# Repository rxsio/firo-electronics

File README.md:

# Hello
This is a test README to confirm proper branch setup

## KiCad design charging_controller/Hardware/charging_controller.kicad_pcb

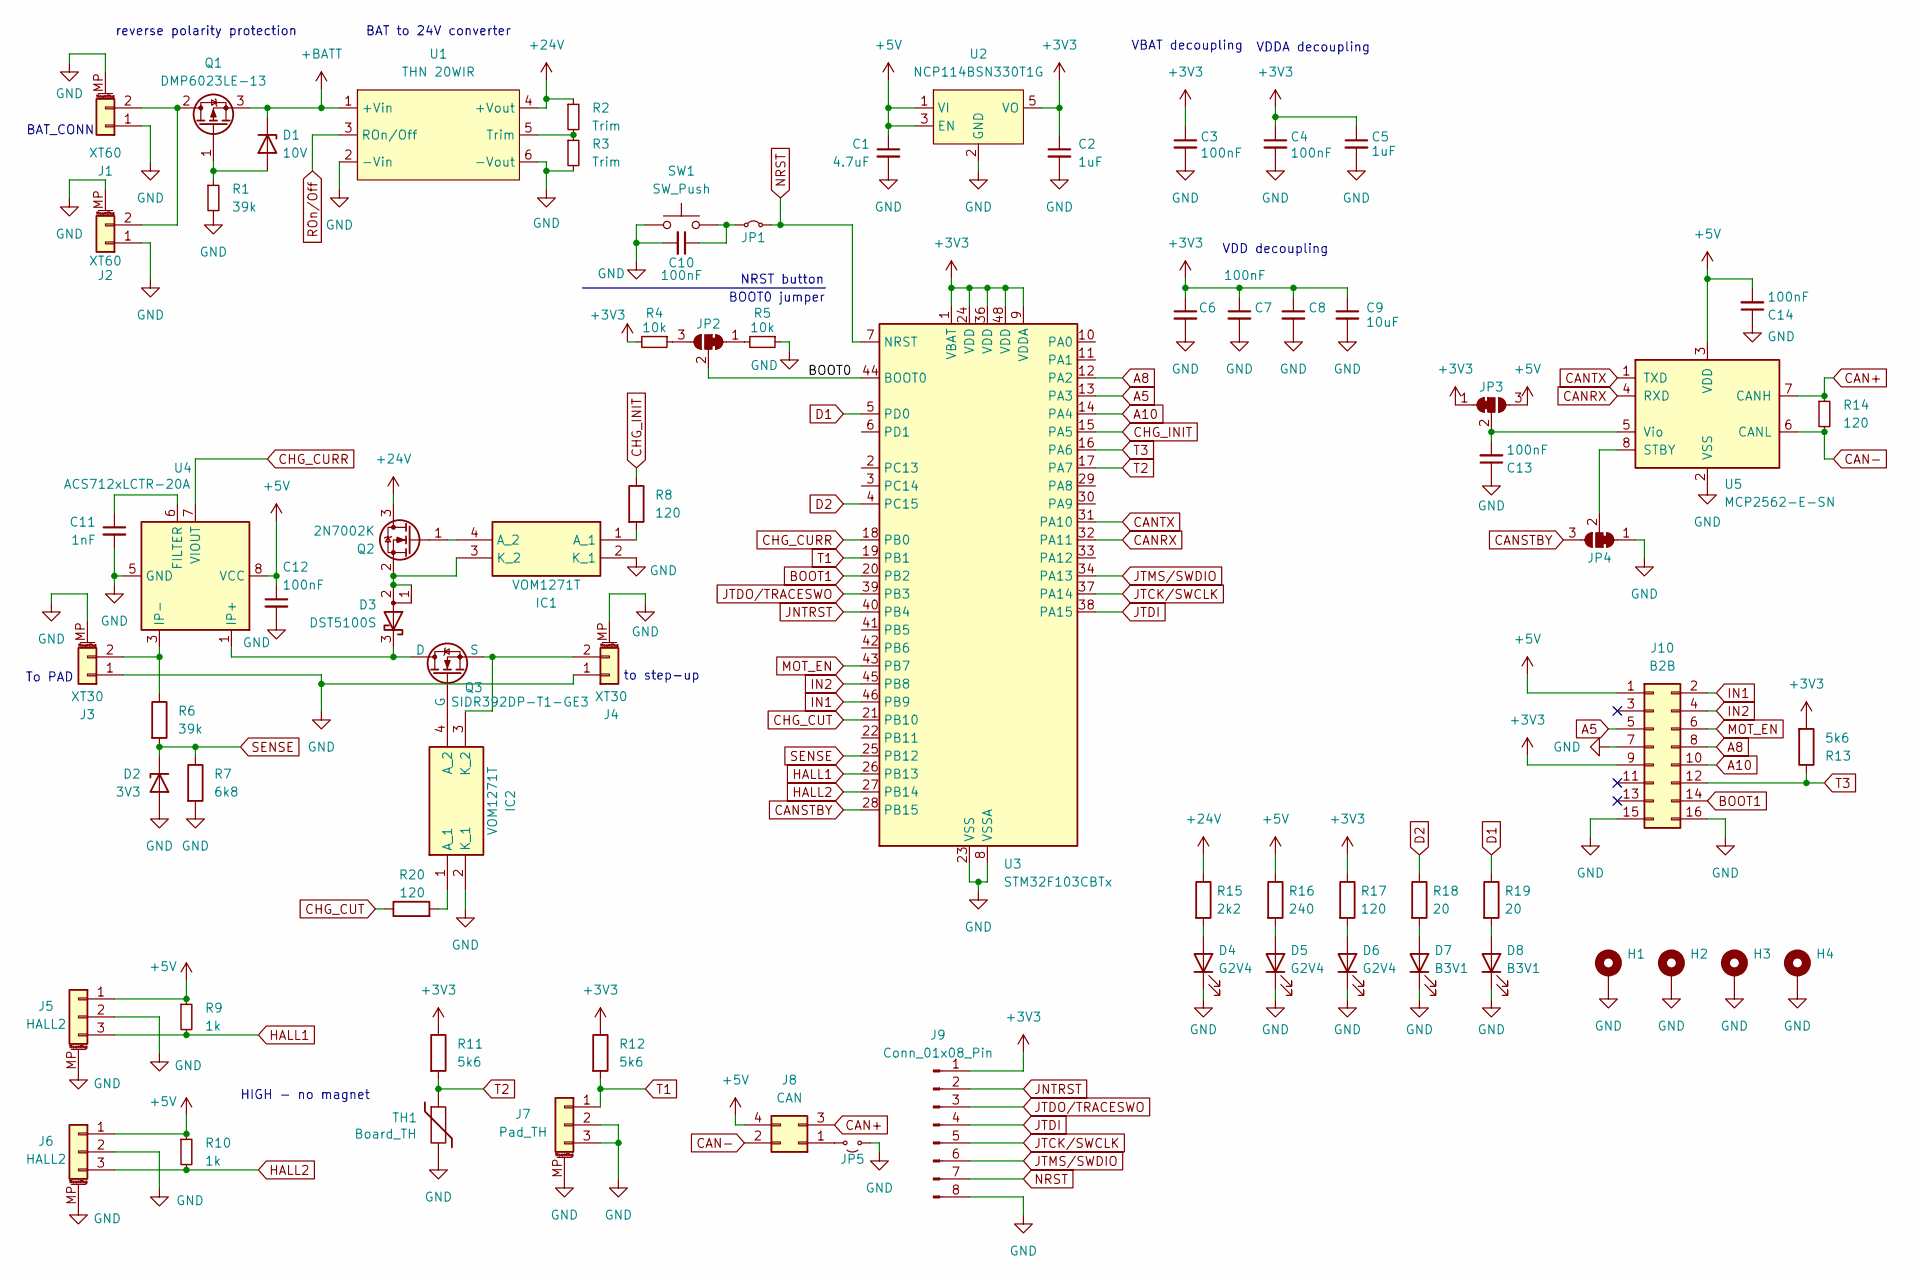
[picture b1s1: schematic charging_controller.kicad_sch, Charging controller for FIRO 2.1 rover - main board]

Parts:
C1: 4.7uF; C_0805_2012Metric
C2, C5: 1uF; C_0805_2012Metric
C3, C4, C6, C7, C8, C10, C12, C13, C14: 100nF; C_0402_1005Metric
C9: 10uF; C_0805_2012Metric
C11: 1nF; C_0805_2012Metric
D1: 10V; D_SOD-128
D2: 3V3; D_SOD-523
D3: DST5100S; TO-277B
D4, D5, D6: G2V4; LED_0805_2012Metric
D7, D8: B3V1; LED_0805_2012Metric
H1, H2, H3, H4: MountingHole_Pad; MountingHole_3.2mm_M3_Pad_Via
IC1, IC2: VOM1271T; SOP254P675X240-4N; Manufacturer_Part_Number VOM1271T
J1: XT60; AMASS_XT60PW-F-MP
J2: XT60; AMASS_XT60-F_1x02_P7.20mm_Vertical
J3: XT30; AMASS_XT30PW-M_1x02_P2.50mm_Horizontal
J4: XT30; AMASS_XT30PW-F_1x02_P2.50mm_Horizontal
J5, J6: HALL2; TEConnectivity_RITS_Header_3P_V
J7: Pad_TH; TEConnectivity_RITS_Header_3P_V
J8: CAN; TE_Micro-MaTch_215079-4_2x02_P1.27mm_Vertical
J9: Conn_01x08_Pin; PinHeader_2x04_P2.54mm_Vertical
J10: B2B; PinHeader_2x08_P2.54mm_Vertical
JP1: Jumper_2_Small_Bridged; SolderJumper-2_P1.3mm_Bridged_RoundedPad1.0x1.5mm
JP2, JP3, JP4: SolderJumper_3_Bridged12; SolderJumper-3_P1.3mm_Bridged12_RoundedPad1.0x1.5mm
JP5: Jumper_2_Small_Open; SolderJumper-2_P1.3mm_Open_RoundedPad1.0x1.5mm
Q1: DMP6023LE-13; SOT-223-3_TabPin2
Q2: 2N7002K; SOT-23
Q3: SIDR392DP-T1-GE3; PowerPAK_SO-8DC for VISHAY SIDR392DP-T1-GE3
R1, R6: 39k; R_0603_1608Metric
R2, R3: Trim; R_0603_1608Metric
R4, R5: 10k; R_0402_1005Metric
R7: 6k8; R_0402_1005Metric
R8, R14, R17, R20: 120; R_0805_2012Metric
R9, R10: 1k; R_0402_1005Metric
R11, R12, R13: 5k6; R_0402_1005Metric
R15: 2k2; R_1206_3216Metric
R16: 240; R_0805_2012Metric
R18, R19: 20; R_0805_2012Metric
SW1: SW_Push; SW_SPST_EVQP7C
TH1: Board_TH; R_0603_1608Metric
U1: THN 20WIR; TRACO THN 20WIR
U2: NCP114BSN330T1G; TSOP-5_1.65x3.05mm_P0.95mm
U3: STM32F103CBTx; LQFP-48_7x7mm_P0.5mm
U4: ACS712xLCTR-20A; SOIC-8_3.9x4.9mm_P1.27mm
U5: MCP2562-E-SN; SOIC-8_3.9x4.9mm_P1.27mm

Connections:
+3V3: C2.1, C3.1, C4.1, C5.1, C6.1, C7.1, C8.1, C9.1, J9.1, J10.9, JP3.1 (A), R4.2, R11.1, R12.1, R13.2, R17.1, U2.5 (VO), U3.1 (VBAT), U3.9 (VDDA), U3.24 (VDD), U3.36 (VDD), U3.48 (VDD)
+5V: C1.1, C12.1, C14.2, J5.1, J6.1, J8.4, J10.1, JP3.3 (B), R9.1, R10.1, R16.1, U2.1 (VI), U2.3 (EN), U4.8 (VCC), U5.3 (VDD)
+24V: Q2.3 (D), R2.1, R15.1, U1.4 (+Vout)
+BATT: D1.1 (K), Q1.3 (S), U1.1 (+Vin)
/BOOT0: JP2.2 (C), U3.44 (BOOT0)
A5: J10.5, U3.13 (PA3)
A8: J10.8, U3.12 (PA2)
A10: J10.10, U3.14 (PA4)
BOOT1: J10.14, U3.20 (PB2)
CAN+: J8.3, R14.1, U5.7 (CANH)
CAN-: J8.2, R14.2, U5.6 (CANL)
CANRX: U3.32 (PA11), U5.4 (RXD)
CANSTBY: JP4.3 (B), U3.28 (PB15)
CANTX: U3.31 (PA10), U5.1 (TXD)
CHG_CURR: U3.18 (PB0), U4.7 (VIOUT)
CHG_CUT: R20.1, U3.21 (PB10)
CHG_INIT: R8.1, U3.15 (PA5)
D1: R19.1, U3.5 (PD0)
D2: R18.1, U3.4 (PC15)
GND: C1.2, C2.2, C3.2, C4.2, C5.2, C6.2, C7.2, C8.2, C9.2, C10.2, C11.2, C12.2, C13.1, C14.1, D2.2 (A), D4.1 (K), D5.1 (K), D6.1 (K), D7.1 (K), D8.1 (K), H1.1, H2.1, H3.1, H4.1, IC1.2 (K_1), IC2.2 (K_1), J1.1, J1.MP (MountPin), J2.1, J2.MP (MountPin), J3.1, J3.MP (MountPin), J4.1, J4.MP (MountPin), J5.2, J5.MP (MountPin), J6.2, J6.MP (MountPin), J7.2, J7.3, J7.MP (MountPin), J9.8, J10.7, J10.15, J10.16, JP4.1 (A), JP5.2 (B), R1.2, R3.2, R5.1, R7.2, SW1.1, TH1.2, U1.2 (-Vin), U1.6 (-Vout), U2.2 (GND), U3.8 (VSSA), U3.23 (VSS), U3.35 (VSS), U3.47 (VSS), U4.5 (GND), U5.2 (VSS)
HALL1: J5.3, R9.2, U3.26 (PB13)
HALL2: J6.3, R10.2, U3.27 (PB14)
IN1: J10.2, U3.46 (PB9)
IN2: J10.4, U3.45 (PB8)
JNTRST: J9.2, U3.40 (PB4)
JTCK/SWCLK: J9.5, U3.37 (PA14)
JTDI: J9.4, U3.38 (PA15)
JTDO/TRACESWO: J9.3, U3.39 (PB3)
JTMS/SWDIO: J9.6, U3.34 (PA13)
MOT_EN: J10.6, U3.43 (PB7)
NRST: J9.7, JP1.2 (B), U3.7 (NRST)
unnamed: D1.2 (A), Q1.1 (G), R1.1
unnamed: D3.3 (K), Q3.3 (D), U4.1 (IP+), U4.2 (IP+)
unnamed: D4.2 (A), R15.2
unnamed: D5.2 (A), R16.2
unnamed: D6.2 (A), R17.2
unnamed: D7.2 (A), R18.2
unnamed: D8.2 (A), R19.2
unnamed: IC1.1 (A_1), R8.2
unnamed: IC1.4 (A_2), Q2.1 (G)
unnamed: D3.1 (A), D3.2 (A), IC1.3 (K_2), Q2.2 (S)
unnamed: IC2.1 (A_1), R20.2
unnamed: IC2.4 (A_2), Q3.2 (G)
unnamed: IC2.3 (K_2), J4.2, Q3.1 (S)
unnamed: J1.2, J2.2, Q1.2 (D)
unnamed: J3.2, R6.1, U4.3 (IP-), U4.4 (IP-)
unnamed: J8.1, JP5.1 (A)
unnamed: C10.1, JP1.1 (A), SW1.2
unnamed: JP2.1 (A), R5.2
unnamed: JP2.3 (B), R4.1
unnamed: C13.2, JP3.2 (C), U5.5 (Vio)
unnamed: JP4.2 (C), U5.8 (STBY)
unnamed: R2.2, R3.1, U1.5 (Trim)
unnamed: C11.1, U4.6 (FILTER)
ROn/Off: U1.3 (ROn/Off)
SENSE: D2.1 (K), R6.2, R7.1, U3.25 (PB12)
T1: J7.1, R12.2, U3.19 (PB1)
T2: R11.2, TH1.1, U3.17 (PA7)
T3: J10.12, R13.1, U3.16 (PA6)

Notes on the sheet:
BAT to 24V converter
VDD decoupling
BOOT0 jumper
HIGH - no magnet
VDDA decoupling
VBAT decoupling
To PAD
reverse polarity protection
NRST button
BAT_CONN
to step-up

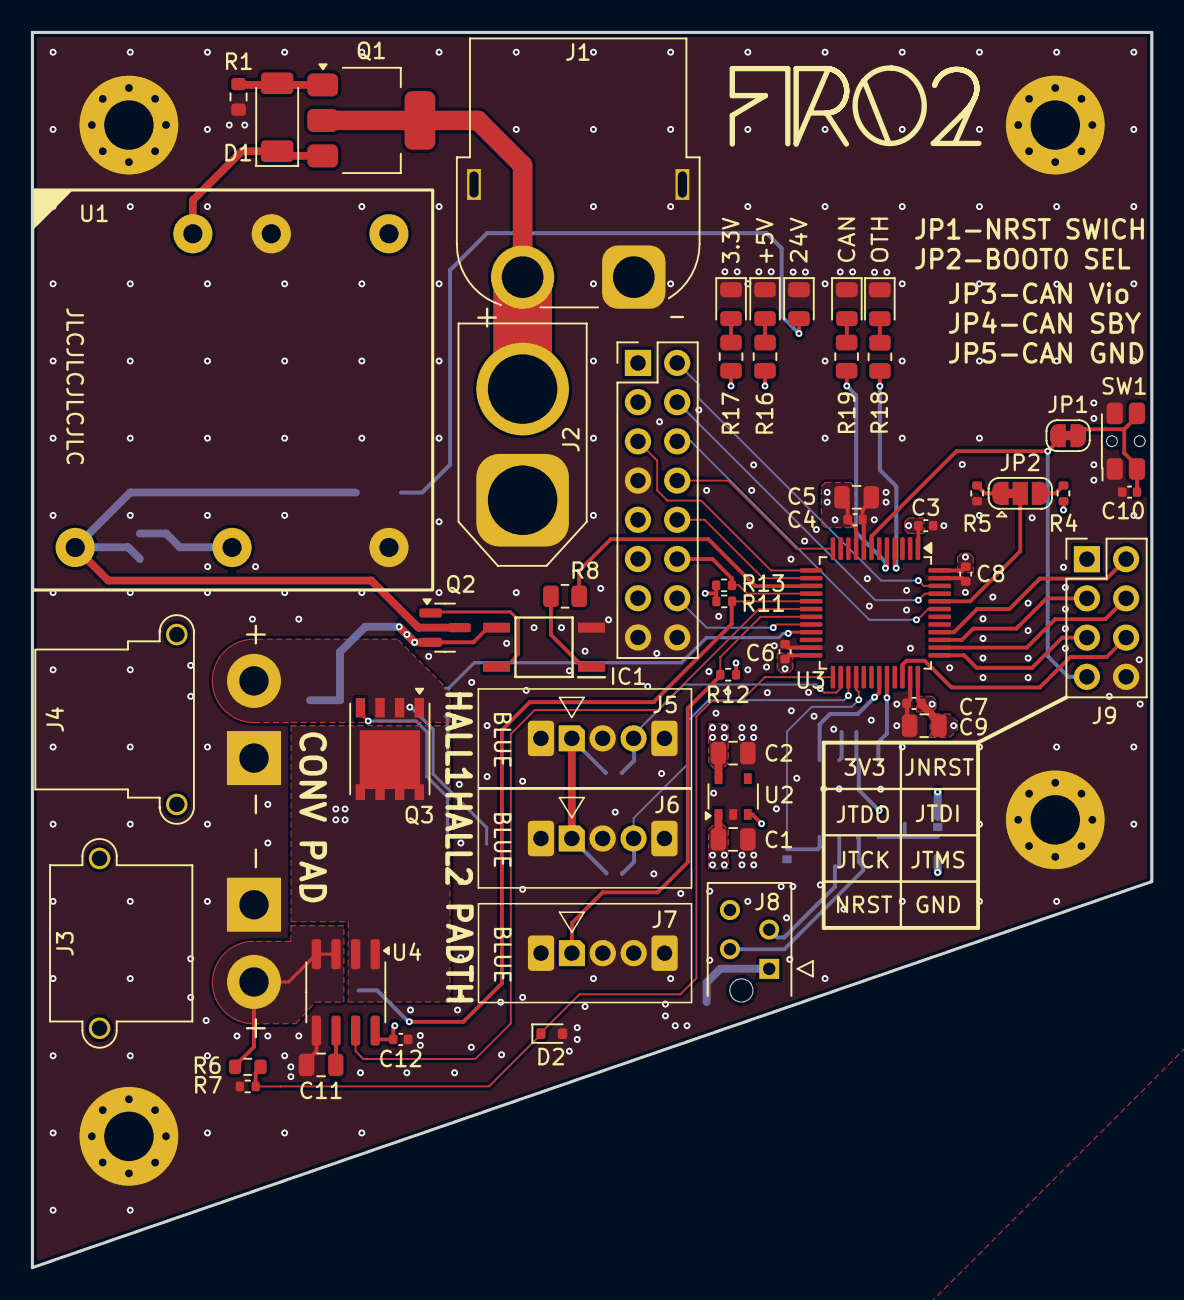
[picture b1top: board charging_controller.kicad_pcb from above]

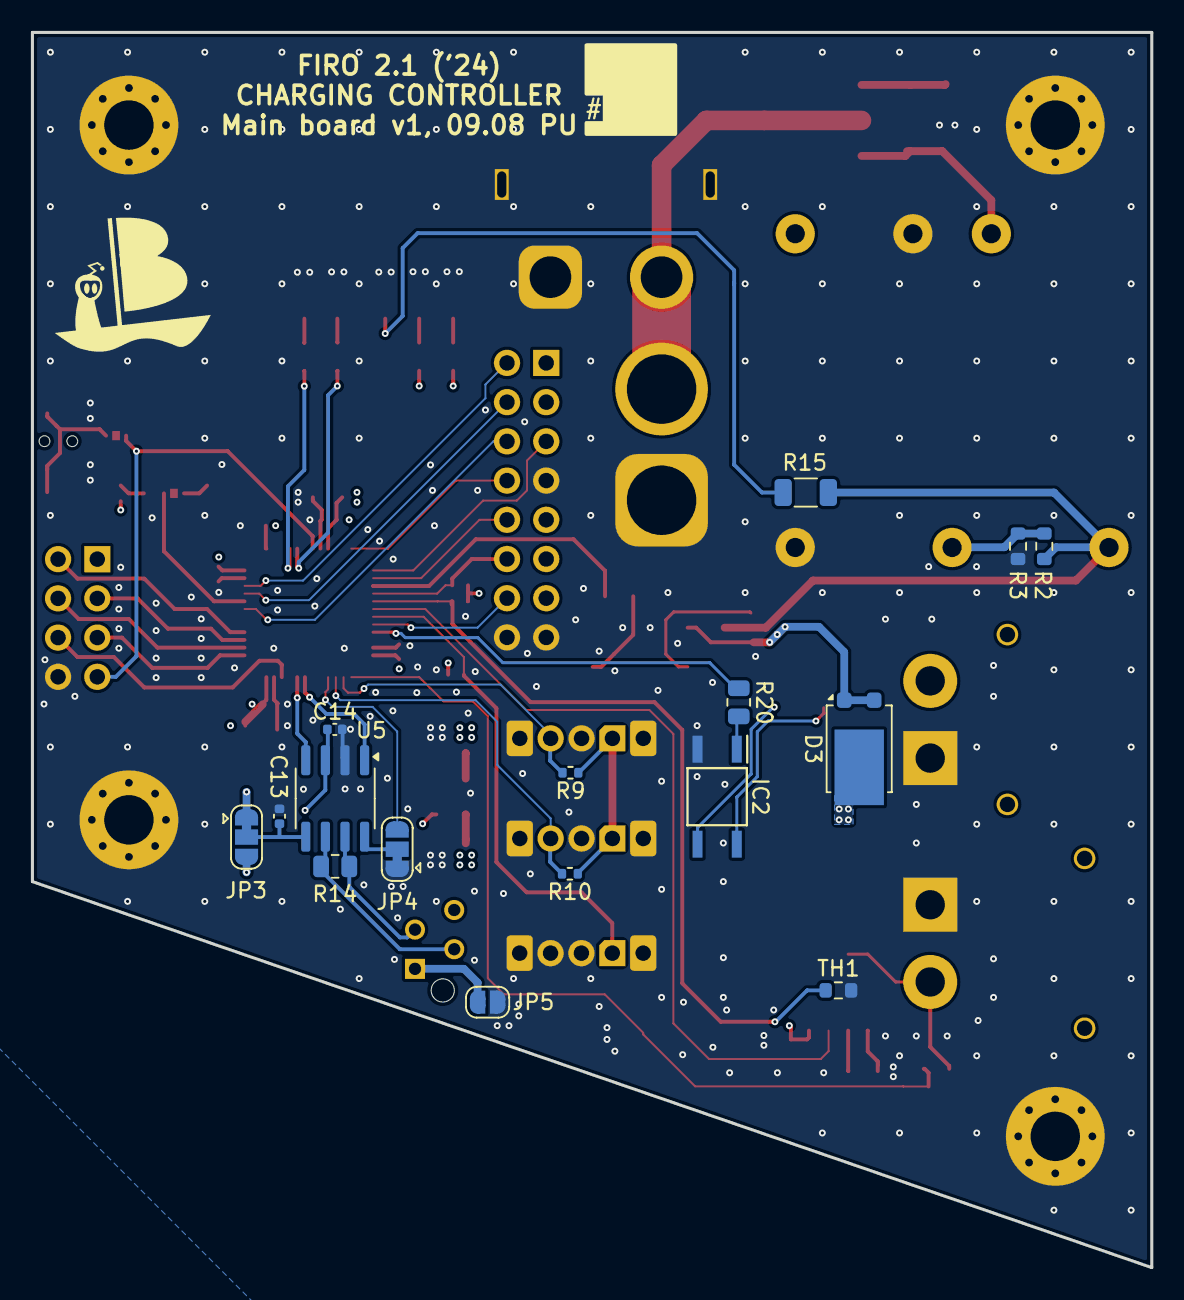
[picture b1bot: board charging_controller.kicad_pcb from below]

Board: 4 copper layers, 72.5 x 80.0 mm, 73 parts (16 on the bottom side), 58 nets.

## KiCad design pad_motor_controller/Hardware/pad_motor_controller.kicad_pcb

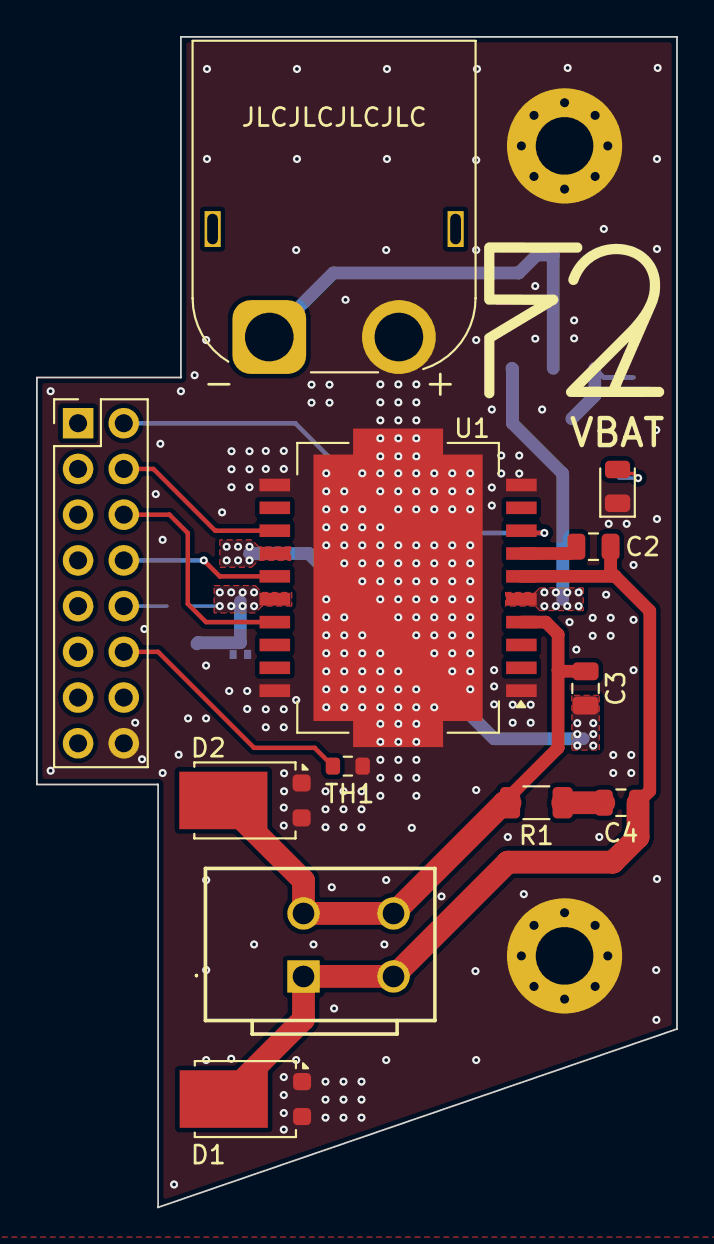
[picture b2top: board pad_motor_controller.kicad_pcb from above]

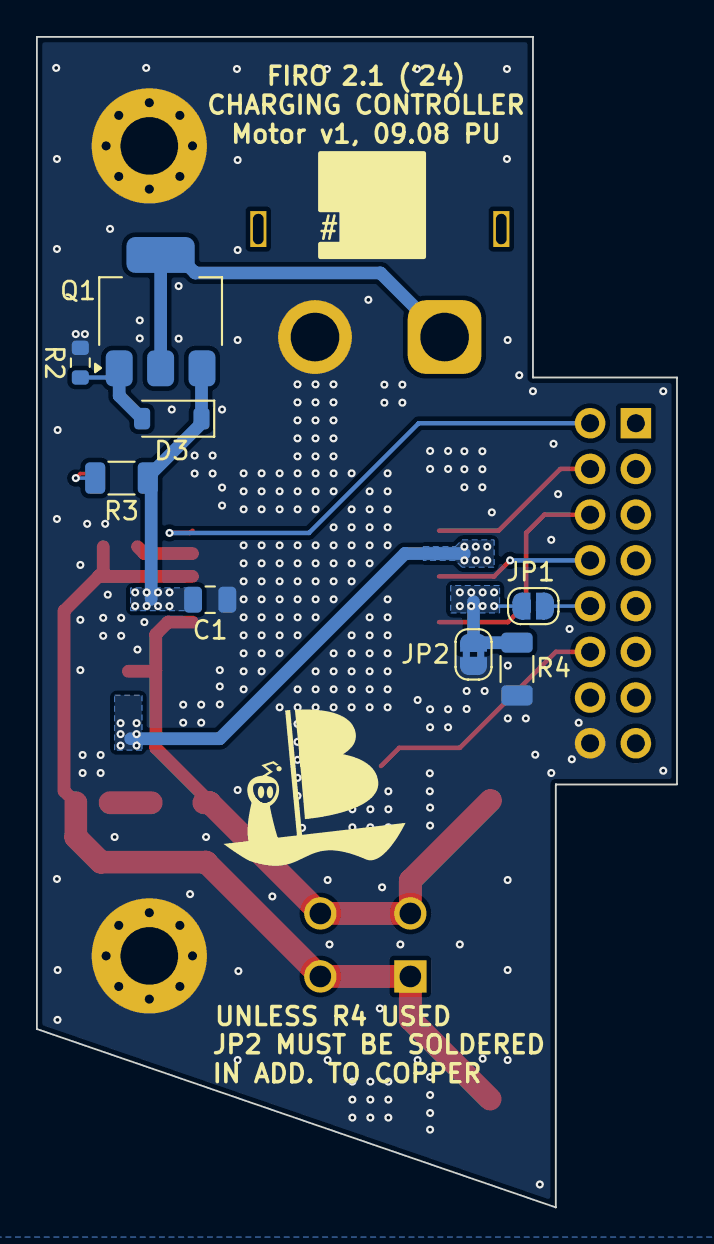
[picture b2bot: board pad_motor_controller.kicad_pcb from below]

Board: 4 copper layers, 35.6 x 65.0 mm, 22 parts (8 on the bottom side), 17 nets.

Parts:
C1: 100nF; C_0805_2012Metric
C2, C3: 10nF; C_0805_2012Metric
C4: ??; C_0805_2012Metric
D1, D2: DST5100S; TO-277B
D3: 10V; D_SOD-123
D4: G2V4; LED_0805_2012Metric
H1, H2: MountingHole_Pad; MountingHole_3.2mm_M3_Pad_Via
J1: ??; WAGO 2601-3102
J2: Conn_01x02_MountingPin; AMASS_XT60PW-M_1x02_P7.20mm_Horizontal
J3: B2B; PinHeader_2x08_P2.54mm_Vertical
JP1: Jumper_2_Small_Open; SolderJumper-2_P1.3mm_Open_RoundedPad1.0x1.5mm
JP2: Jumper_2_Small_Bridged; SolderJumper-2_P1.3mm_Bridged2Bar_RoundedPad1.0x1.5mm
Q1: DMP6023LE-13; SOT-223-3_TabPin2
R1: 10; R_1206_3216Metric
R2: 39k; R_0603_1608Metric
R3: 3k9; R_1206_3216Metric
R4: Current sense (opt); R_1206_3216Metric
TH1: Board_TH; R_0603_1608Metric
U1: L6201PS; HSOP-20-1EP_11.0x15.9mm_P1.27mm_SlugDown

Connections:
+BATT: C1.2, D3.1 (K), Q1.3 (S), R3.1, U1.5 (Vs)
GND: C1.1, D1.1 (A), D1.2 (A), D2.1 (A), D2.2 (A), D4.1 (K), H1.1, H2.1, J2.2, J3.16, JP2.1 (A), R2.2, R4.1, TH1.2, U1.1 (GND), U1.10 (GND), U1.11 (GND), U1.20 (GND), U1.21 (GND)
unnamed: C4.2, R1.1
unnamed: C2.2, C4.1, D1.3 (K), J1.1, U1.6 (OUT1)
unnamed: C3.1, D2.3 (K), J1.2, R1.2, U1.4 (OUT2)
unnamed: D3.2 (A), Q1.1 (G), R2.1
unnamed: D4.2 (A), R3.2
unnamed: J2.1, Q1.2 (D)
unnamed: J3.2, U1.8 (IN1)
unnamed: J3.4, U1.13 (IN2)
unnamed: J3.6, U1.17 (ENABLE)
unnamed: J3.8, U1.15 (Vref)
unnamed: J3.10, JP1.1 (A)
unnamed: J3.12, TH1.1
unnamed: JP1.2 (B), JP2.2 (B), R4.2, U1.16 (SENSE)
unnamed: C2.1, U1.7 (BOOT1)
unnamed: C3.2, U1.14 (BOOT2)

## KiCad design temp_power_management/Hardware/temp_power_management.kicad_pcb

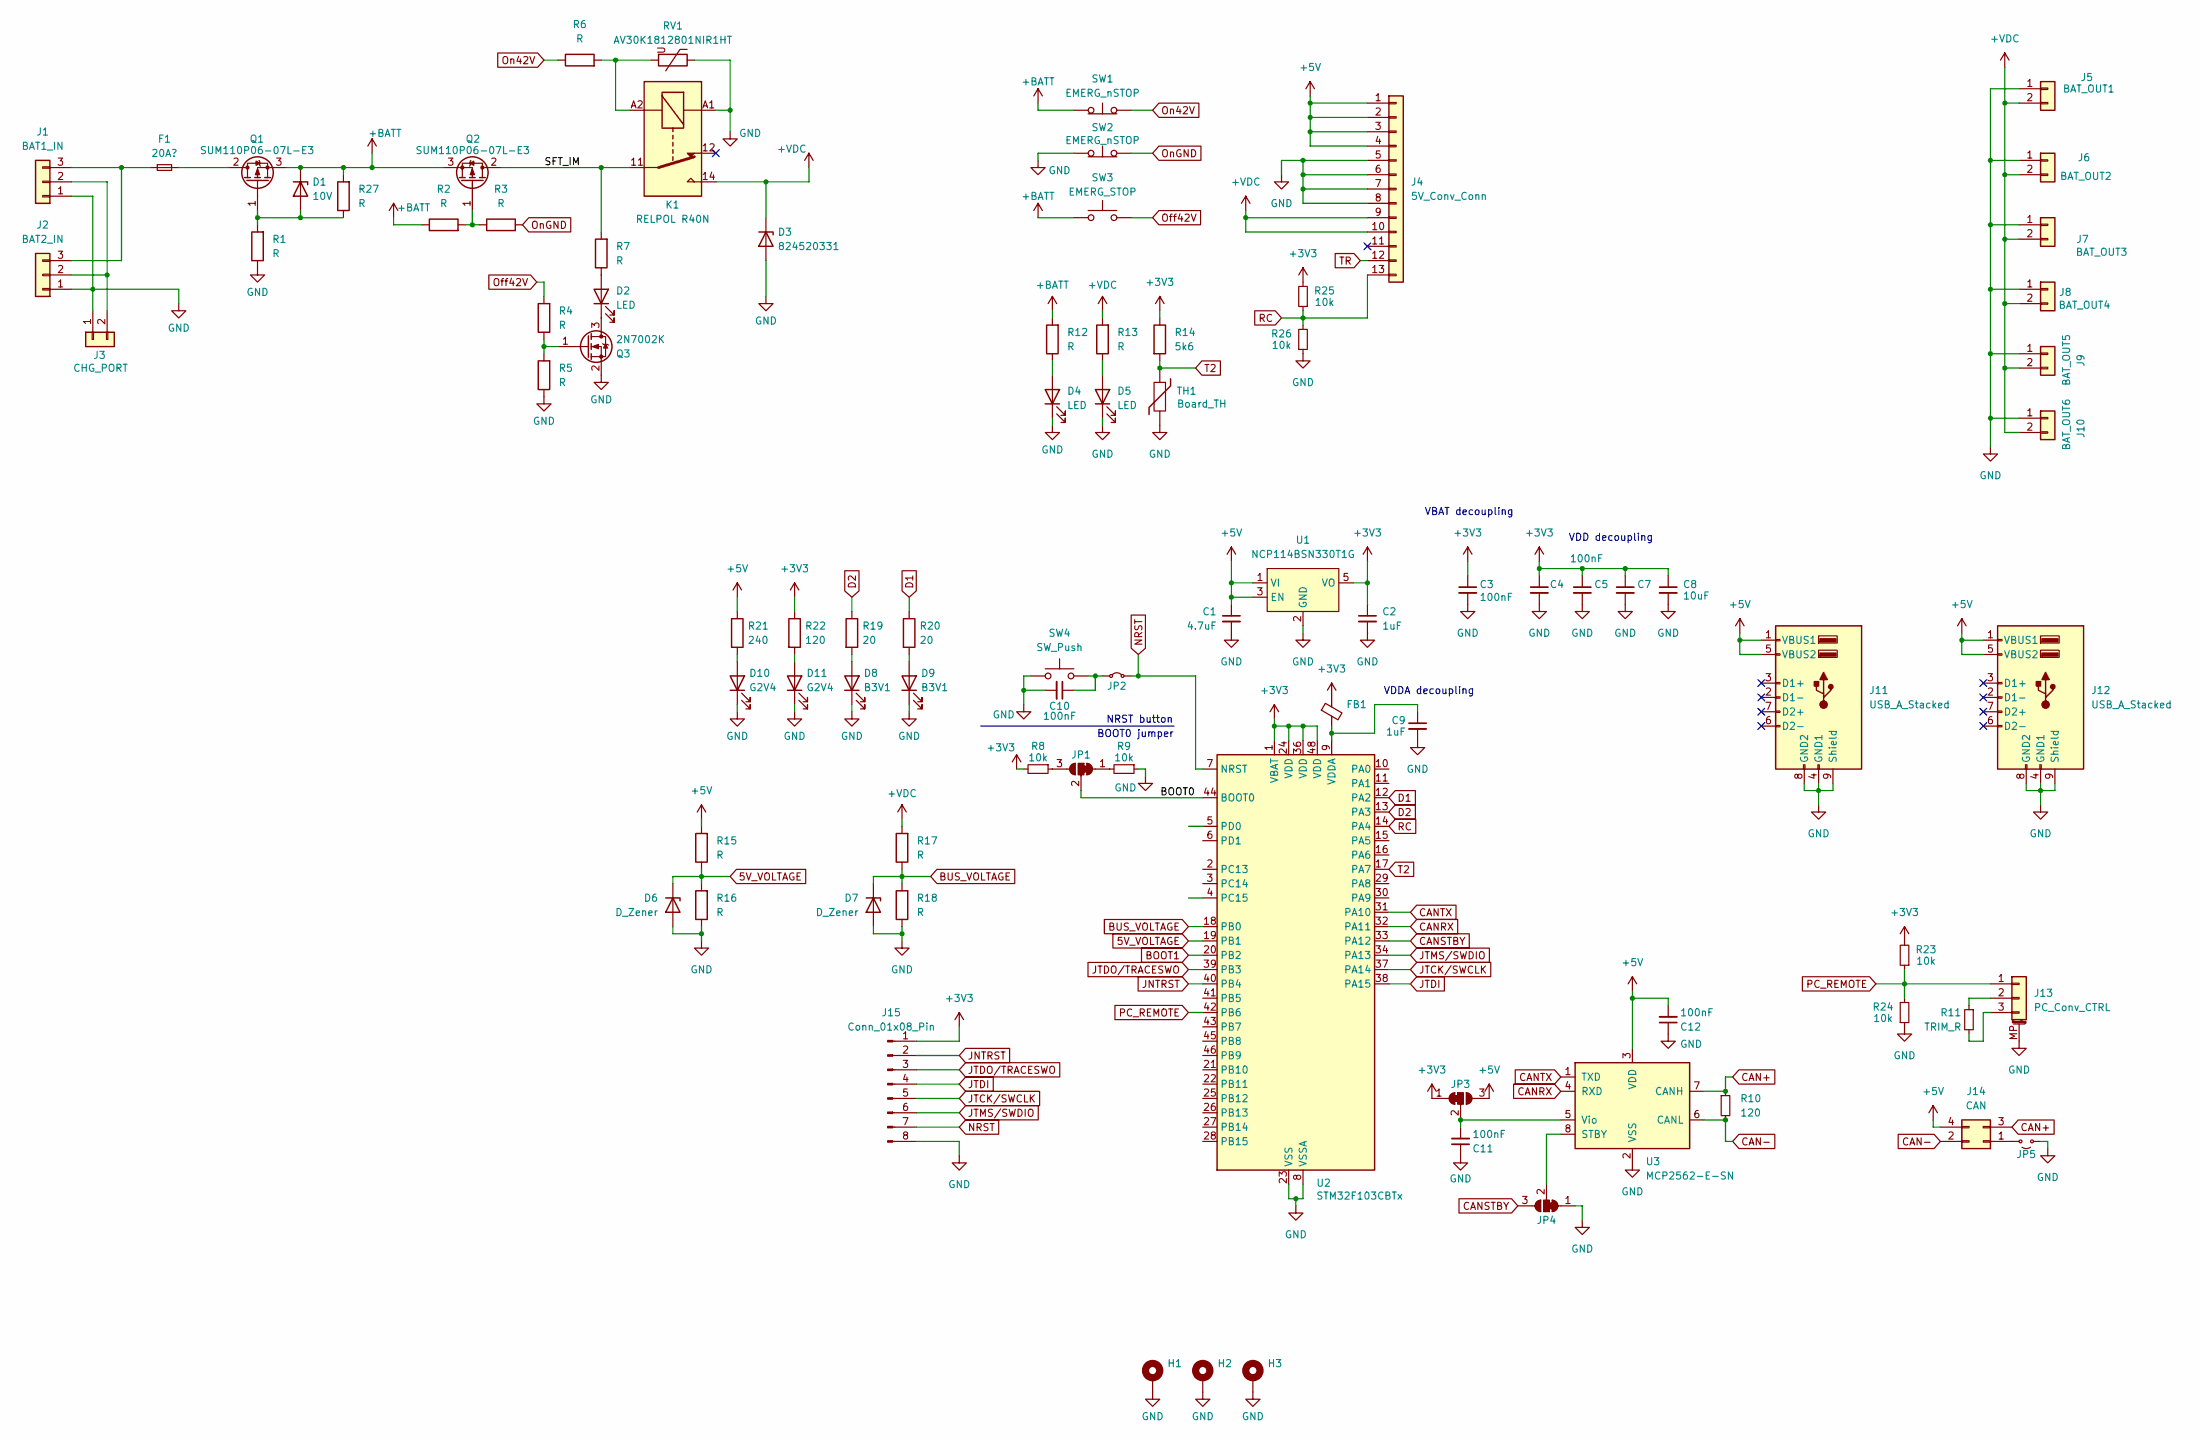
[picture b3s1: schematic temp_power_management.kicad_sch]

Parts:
C1: 4.7uF; C_0805_2012Metric
C2, C9: 1uF; C_0805_2012Metric
C3, C4, C5, C7, C10, C11, C12: 100nF; C_0402_1005Metric
C8: 10uF; C_0805_2012Metric
D1: 10V; D_SOD-128
D2, D4, D5: LED; LED_0805_2012Metric
D3: 824520331; D_SOD-128
D6, D7: D_Zener; D_SOD-523
D8, D9: B3V1; LED_0805_2012Metric
D10, D11: G2V4; LED_0805_2012Metric
F1: 20A?; firo_fuse
FB1: FerriteBead_Small; R_0402_1005Metric_Pad0.72x0.64mm_HandSolder
H1, H2, H3: MountingHole_Pad; MountingHole_3.2mm_M3_Pad_Via
J1: BAT1_IN; AMASS_MR60-M_1x03_Vertical
J2: BAT2_IN; AMASS_MR60-M_1x03_Vertical
J3: CHG_PORT; AMASS_XT30U-M_1x02_P5.0mm_Vertical
J4: 5V_Conv_Conn; MeanWell NID100-R3
J5: BAT_OUT1; AMASS_XT60-F_1x02_P7.20mm_Vertical
J6: BAT_OUT2; AMASS_XT60-F_1x02_P7.20mm_Vertical
J7: BAT_OUT3; AMASS_XT60-F_1x02_P7.20mm_Vertical
J8: BAT_OUT4; AMASS_XT60-F_1x02_P7.20mm_Vertical
J9: BAT_OUT5; AMASS_XT60-F_1x02_P7.20mm_Vertical
J10: BAT_OUT6; AMASS_XT60-F_1x02_P7.20mm_Vertical
J11, J12: USB_A_Stacked; USB_A_CUI_UJ2-ADH-TH_Horizontal_Stacked
J13: PC_Conv_CTRL; TEConnectivity_RITS_Header_3P_V
J14: CAN; TE_Micro-MaTch_215079-4_2x02_P1.27mm_Vertical
J15: Conn_01x08_Pin; PinHeader_2x04_P2.54mm_Vertical
JP1, JP3, JP4: SolderJumper_3_Bridged12; SolderJumper-3_P1.3mm_Bridged12_RoundedPad1.0x1.5mm
JP2: Jumper_2_Small_Bridged; SolderJumper-2_P1.3mm_Bridged_RoundedPad1.0x1.5mm
JP5: Jumper_2_Small_Open; SolderJumper-2_P1.3mm_Open_RoundedPad1.0x1.5mm
K1: RELPOL R40N; Relpol R40N
Q1, Q2: SUM110P06-07L-E3; TO-263-2
Q3: 2N7002K; SOT-23
R1, R4, R5, R15, R16, R17, R18, R27: R; R_0402_1005Metric
R2, R3: R; R_0805_2012Metric
R6, R7, R12, R13: R; R_1206_3216Metric
R8, R9, R23, R24, R25, R26: 10k; R_0402_1005Metric
R10, R22: 120; R_0805_2012Metric
R11: TRIM_R; R_0805_2012Metric
R14: 5k6; R_0402_1005Metric
R19, R20: 20; R_0805_2012Metric
R21: 240; R_0805_2012Metric
RV1: AV30K1812801NIR1HT; R_1812_4532Metric
SW1, SW2: EMERG_nSTOP; WAGO 2601-3102
SW3: EMERG_STOP; WAGO 2601-3102
SW4: SW_Push; SW_SPST_EVQP7C
TH1: Board_TH; R_0603_1608Metric
U1: NCP114BSN330T1G; TSOP-5_1.65x3.05mm_P0.95mm
U2: STM32F103CBTx; LQFP-48_7x7mm_P0.5mm
U3: MCP2562-E-SN; SOIC-8_3.9x4.9mm_P1.27mm

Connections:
5V_VOLTAGE: D6.1 (K), R15.1, R16.2, U2.19 (PB1)
+3V3: C2.1, C3.1, C4.1, C5.1, C7.1, C8.1, FB1.1, J15.1, JP3.1 (A), R8.2, R14.1, R22.1, R23.2, R25.2, U1.5 (VO), U2.1 (VBAT), U2.24 (VDD), U2.36 (VDD), U2.48 (VDD)
+5V: C1.1, C12.2, J4.1, J4.2, J4.3, J4.4, J11.1 (VBUS1), J11.5 (VBUS2), J12.1 (VBUS1), J12.5 (VBUS2), J14.4, JP3.3 (B), R15.2, R21.1, U1.1 (VI), U1.3 (EN), U3.3 (VDD)
+BATT: D1.1 (K), Q1.3 (S), Q2.3 (S), R2.1, R12.2, R27.2, SW1.1 (A), SW3.1
+VDC: D3.1 (K), J4.9, J4.10, J5.2, J6.2, J7.2, J8.2, J9.2, J10.2, K1.14, R13.2, R17.2
/BOOT0: JP1.2 (C), U2.44 (BOOT0)
/SFT_IM: K1.11, Q2.2 (D), R7.2
BOOT1: U2.20 (PB2)
BUS_VOLTAGE: D7.1 (K), R17.1, R18.2, U2.18 (PB0)
CAN+: J14.3, R10.1, U3.7 (CANH)
CAN-: J14.2, R10.2, U3.6 (CANL)
CANRX: U2.32 (PA11), U3.4 (RXD)
CANSTBY: JP4.3 (B), U2.33 (PA12)
CANTX: U2.31 (PA10), U3.1 (TXD)
D1: R20.1, U2.12 (PA2)
D2: R19.1, U2.13 (PA3)
GND: C1.2, C2.2, C3.2, C4.2, C5.2, C7.2, C8.2, C9.2, C10.2, C11.1, C12.1, D3.2 (A), D4.1 (K), D5.1 (K), D6.2 (A), D7.2 (A), D8.1 (K), D9.1 (K), D10.1 (K), D11.1 (K), H1.1, H2.1, H3.1, J1.1, J2.1, J3.1, J4.5, J4.6, J4.7, J4.8, J5.1, J6.1, J7.1, J8.1, J9.1, J10.1, J11.4 (GND1), J11.8 (GND2), J11.9 (Shield), J12.4 (GND1), J12.8 (GND2), J12.9 (Shield), J13.MP (MountPin), J15.8, JP4.1 (A), JP5.2 (B), K1.A1, Q3.2 (S), R1.1, R5.1, R9.1, R16.1, R18.1, R24.1, R26.1, RV1.1, SW2.1 (A), SW4.1, TH1.2, U1.2 (GND), U2.8 (VSSA), U2.23 (VSS), U2.35 (VSS), U2.47 (VSS), U3.2 (VSS)
JNTRST: J15.2, U2.40 (PB4)
JTCK/SWCLK: J15.5, U2.37 (PA14)
JTDI: J15.4, U2.38 (PA15)
JTDO/TRACESWO: J15.3, U2.39 (PB3)
JTMS/SWDIO: J15.6, U2.34 (PA13)
NRST: J15.7, JP2.2 (B), U2.7 (NRST)
unnamed: D1.2 (A), Q1.1 (G), R1.2, R27.1
unnamed: D2.2 (A), R7.1
unnamed: D2.1 (K), Q3.3 (D)
unnamed: D4.2 (A), R12.1
unnamed: D5.2 (A), R13.1
unnamed: D8.2 (A), R19.2
unnamed: D9.2 (A), R20.2
unnamed: D10.2 (A), R21.2
unnamed: D11.2 (A), R22.2
unnamed: J1.2, J2.2, J3.2
unnamed: F1.1, J1.3, J2.3
unnamed: J13.2, R11.1
unnamed: J13.3, R11.2
unnamed: J14.1, JP5.1 (A)
unnamed: JP1.1 (A), R9.2
unnamed: JP1.3 (B), R8.1
unnamed: C10.1, JP2.1 (A), SW4.2
unnamed: C11.2, JP3.2 (C), U3.5 (Vio)
unnamed: JP4.2 (C), U3.8 (STBY)
unnamed: K1.A2, R6.2, RV1.2
unnamed: F1.2, Q1.2 (D)
unnamed: Q2.1 (G), R2.2, R3.1
unnamed: Q3.1 (G), R4.1, R5.2
unnamed: C9.1, FB1.2, U2.9 (VDDA)
Off42V: R4.2, SW3.2
On42V: R6.1, SW1.2 (B)
OnGND: R3.2, SW2.2 (B)
PC_REMOTE: J13.1, R23.1, R24.2, U2.42 (PB6)
RC: J4.13, R25.1, R26.2, U2.14 (PA4)
T2: R14.2, TH1.1, U2.17 (PA7)
TR: J4.12

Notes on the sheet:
VBAT decoupling
BOOT0 jumper
VDD decoupling
NRST button
VDDA decoupling

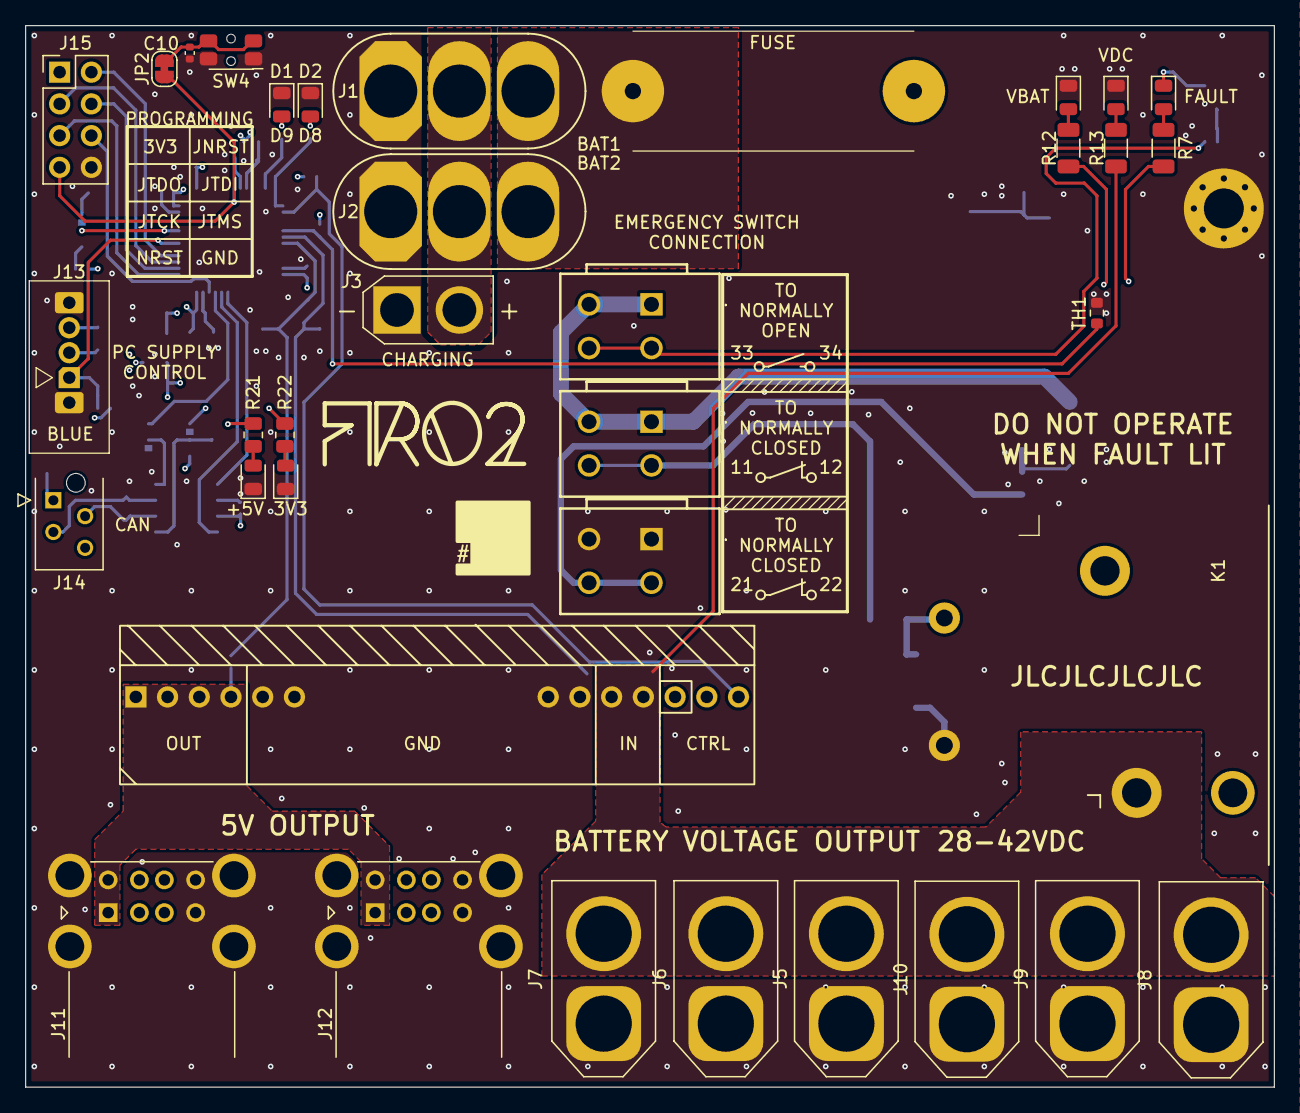
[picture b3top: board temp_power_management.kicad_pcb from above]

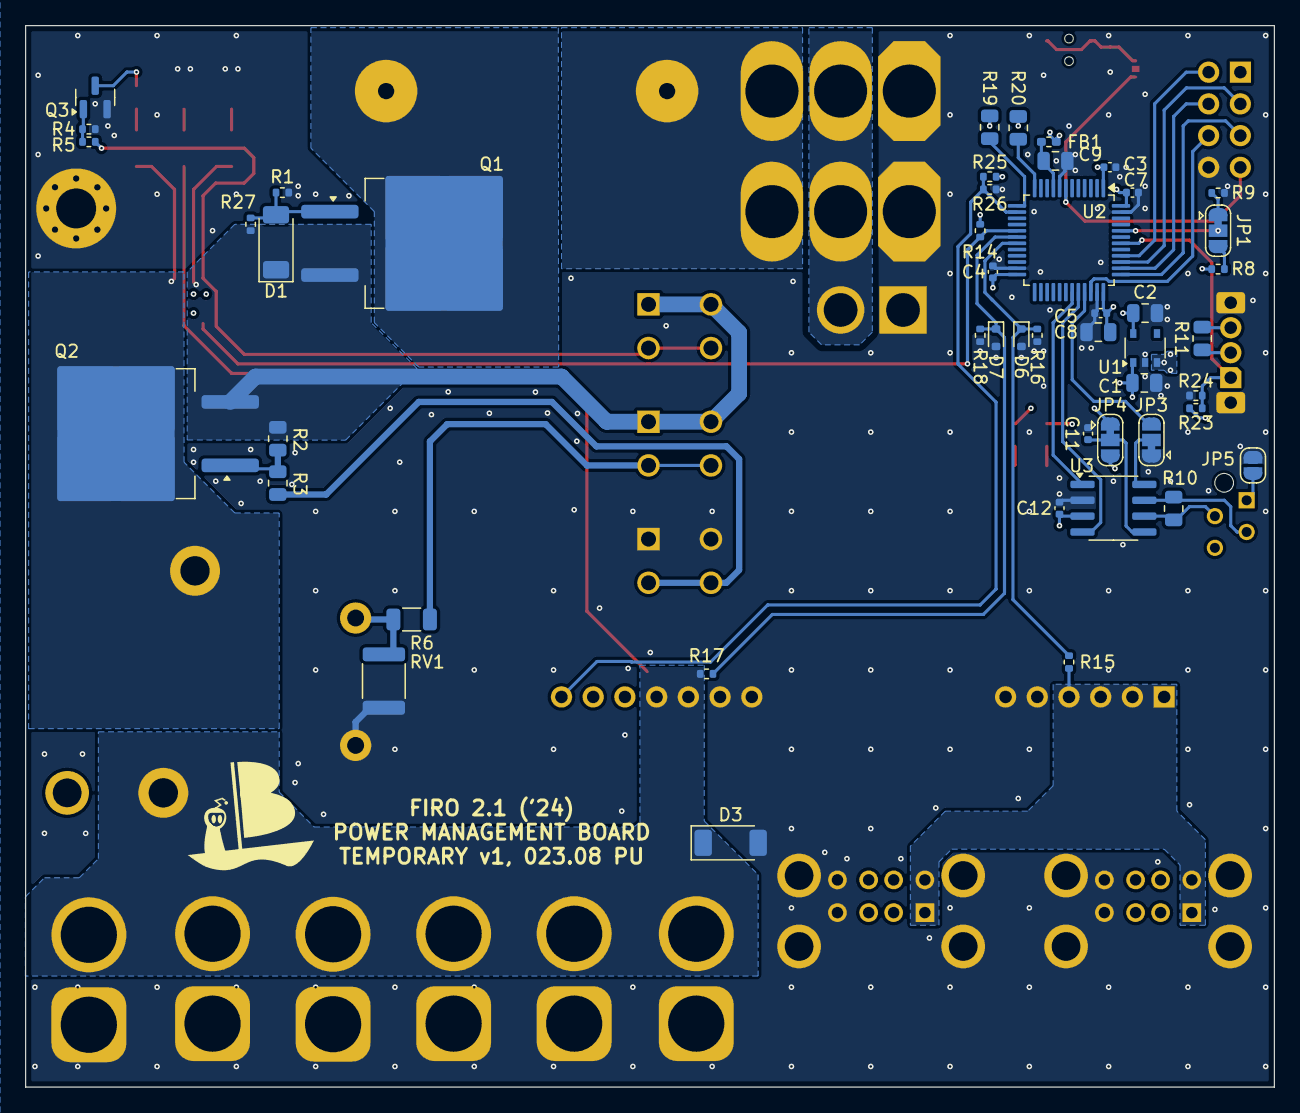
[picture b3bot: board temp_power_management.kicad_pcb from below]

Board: 4 copper layers, 100.0 x 85.0 mm, 85 parts (48 on the bottom side), 52 nets.
